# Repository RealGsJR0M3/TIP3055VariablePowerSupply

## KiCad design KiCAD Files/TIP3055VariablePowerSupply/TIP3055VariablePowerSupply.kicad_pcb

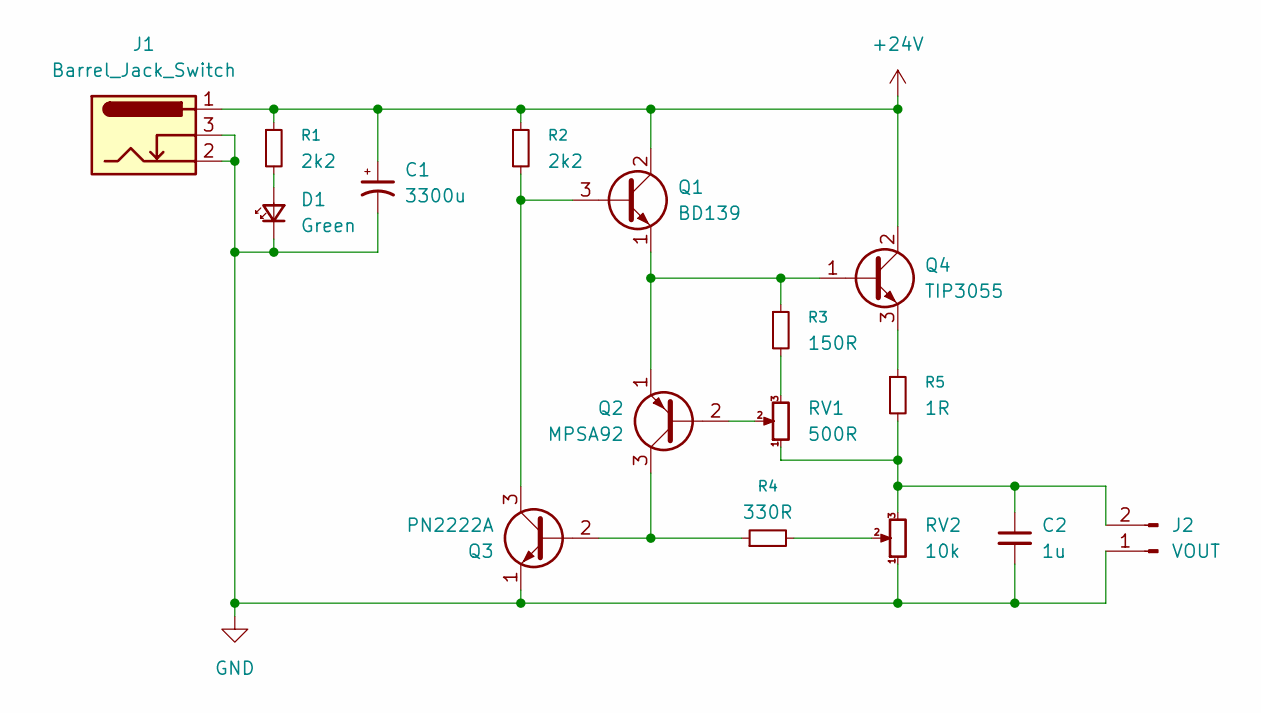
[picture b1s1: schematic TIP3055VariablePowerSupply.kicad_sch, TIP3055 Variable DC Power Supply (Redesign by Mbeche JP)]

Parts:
C1: 3300u; CP_Radial_D16.0mm_P7.50mm
C2: 1u; CP_Radial_D5.0mm_P2.00mm
D1: Green; LED_D5.0mm
J1: Barrel_Jack_Switch; BarrelJack_Kycon_KLDX-0202-xC_Horizontal
J2: VOUT; TerminalBlock_MaiXu_MX126-5.0-02P_1x02_P5.00mm
Q1: BD139; TO-126-3_Vertical
Q2: MPSA92; TO-92_Inline
Q3: PN2222A; TO-92_Inline
Q4: TIP3055; TO-218-3_Vertical
R1, R2: 2k2; R_Axial_DIN0309_L9.0mm_D3.2mm_P15.24mm_Horizontal
R3: 150R; R_Axial_DIN0207_L6.3mm_D2.5mm_P10.16mm_Horizontal
R4: 330R; R_Axial_DIN0207_L6.3mm_D2.5mm_P10.16mm_Horizontal
R5: 1R; R_Axial_Power_L20.0mm_W6.4mm_P25.40mm
RV1: 500R; Potentiometer_Alps_RK09Y11_Single_Horizontal
RV2: 10k; Potentiometer_Alps_RK09Y11_Single_Horizontal

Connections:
+24V: C1.1, J1.1, Q1.2 (C), Q4.2 (C), R1.1, R2.1
GND: C1.2, C2.2, D1.1 (K), J1.2, J1.3, J2.1, Q3.1 (E), RV2.1
unnamed: D1.2 (A), R1.2
unnamed: C2.1, J2.2, R5.2, RV1.1, RV2.3
unnamed: Q1.3 (B), Q3.3 (C), R2.2
unnamed: Q1.1 (E), Q2.1 (E), Q4.1 (B), R3.1
unnamed: Q2.2 (B), RV1.2
unnamed: Q2.3 (C), Q3.2 (B), R4.1
unnamed: Q4.3 (E), R5.1
unnamed: R3.2, RV1.3
unnamed: R4.2, RV2.2

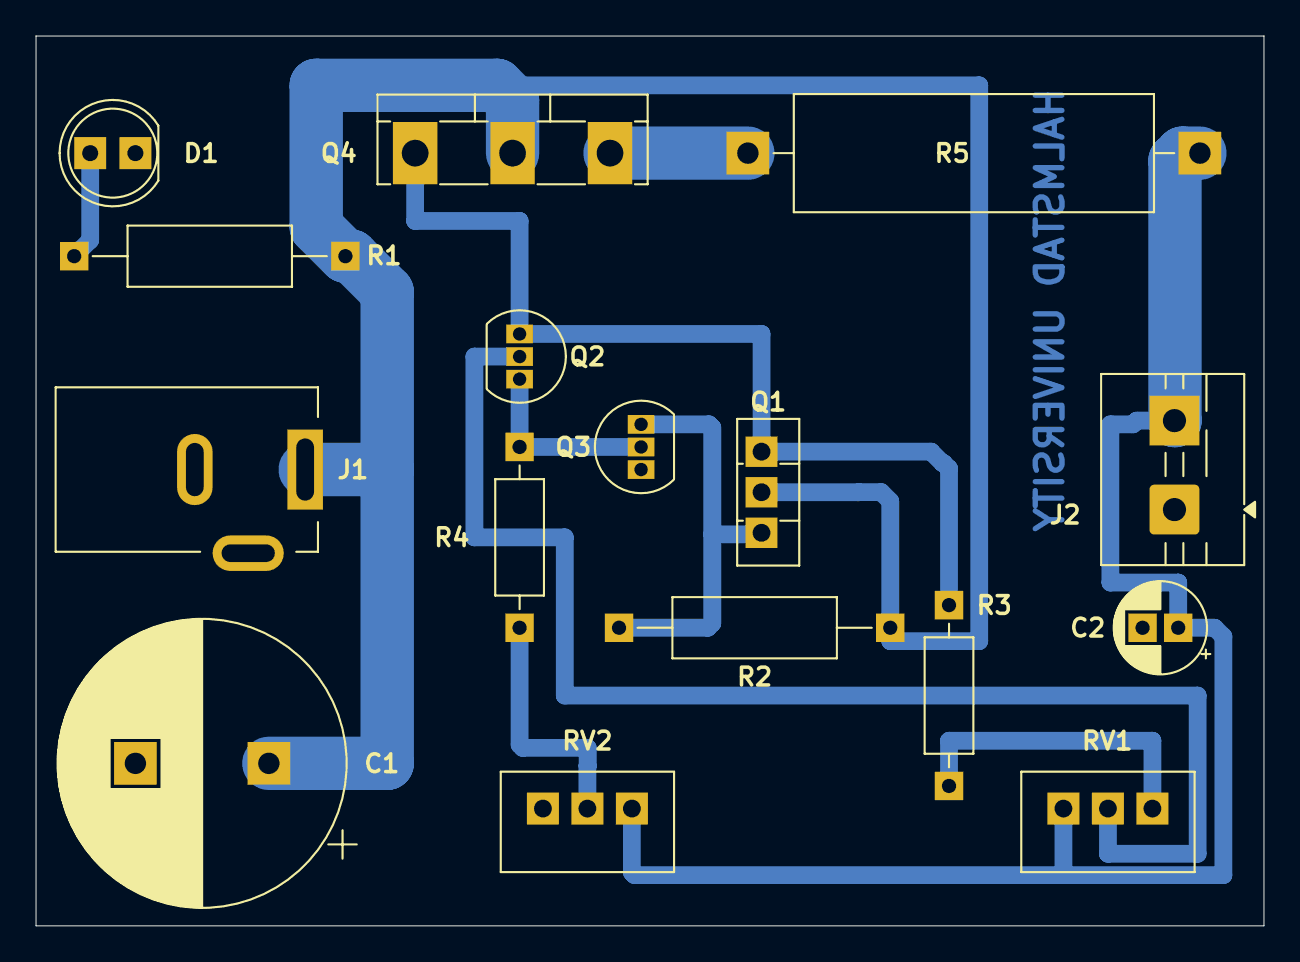
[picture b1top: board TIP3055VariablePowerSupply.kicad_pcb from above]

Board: 2 copper layers, 69.0 x 50.0 mm, 16 parts (0 on the bottom side), 11 nets.

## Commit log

2025-04-20 Updated Schematic Diagram
2025-04-21 Updated Schematic Diagram & Assigned Footprints
2025-04-21 Updated PCB Design
2025-04-24 Updated Images of Design
